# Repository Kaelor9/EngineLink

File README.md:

<h1 align="center">EngineLink</h1>

<p align="center">
  Dual-engine marine fuel monitoring on a custom ESP32-S3 board. It reads two engines over J1708, either Volvo Penta KAD / EDC I or SAE J1587. It shows live fuel flow on your phone and records every engine run, without an app, internet or cloud.
</p>

<p align="center">

</p>

<p align="center">
  
  <br>
  <sub>The phone app served by the board. <a href="https://kaelor9.github.io/EngineLink/demo/">Open the live demo</a> to use it in your browser against a simulated boat.</sub>
</p>

---

## About

**EngineLink** is a dedicated onboard device for boats with two engines. It reads fuel and engine data from two separate J1708 engine interfaces, processes it locally and serves a clean web app straight from the device.

The goal is **useful and trustworthy fuel consumption** rather than raw frames on a screen. If the engines do not send a value, or it is stale or invalid, EngineLink shows **—** and explains why. It never shows a made-up 0.

It is developed for a Fairline Targa 34 with 2 × **Volvo Penta KAD300 (EDC I)**. These engines use Volvo's request/response protocol. Scalings come from the owner's VODIA analysis. See [docs/KAD300_EDC1.md](docs/KAD300_EDC1.md).

---

## Why EngineLink?

Marine engine displays rarely show combined consumption, economy per nautical mile or a history you can export. Generic ESP32 boards need extra isolation and protection before they can be connected to an engine bus.

EngineLink combines both on one board:

- **galvanically isolated** J1708 transceivers, one per engine
- An isolated NMEA 2000 interface for GPS speed and time
- microSD storage for raw data, engine runs and calibration captures
- Its own Wi-Fi network, so it works with no router and no internet
- A phone-friendly web app stored on the device

---

## Key Features

- **Phone app "Engine Link":** Trip, Economy, Tank, History and Engines, add it to the home screen. Light, dark and night themes, metric or imperial, any currency
- **Live fuel flow:** per engine and combined L/h (KAD index 289 or J1587 PID 183)
- **Automatic trips** with notes (people, sea, wind), combine/split and CSV export
- **Fuel log and tank:** fuel aboard with an honest ±, range at the current speed
- **Self-calibrating fuel figures:** weighted fit over all fill-ups (topped up / clicked off), separate correction for idle, part load and cruise, odd fill-ups caught, every trip recalculated
- **Economy:** best cruising speed, trip planner, season statistics per RPM band, engine health trend
- **Volvo Penta KAD / EDC I:** VODIA scaling, passive decoding of an EDC display, or opt-in read-only polling
- **Calibration tools:** voltage check against a multimeter, fuel scale check, gear learned at the dock
- **Checked engine data:** physical limits and jump confirmation on every answer, short gaps bridged, faster reading while the throttle moves
- **Fuel economy:** L/nm when NMEA 2000 GPS speed is available
- **Lifetime totals** with engine hours that survive restarts and recalculate after calibration
- **Bus discovery:** every parameter your ECUs actually answer or send, with raw bytes
- **Guided engine test:** record steady RPM stages with your own reference readings, export CSV
- **Two Wi-Fi modes:** EngineLink's own network at `192.168.4.1` (factory default), or on the boat router at the address the router gives it. If the router is lost, EngineLink brings its own network back within two minutes and returns to the router by itself. Transmit power is tuned automatically.
- **Firmware updates from GitHub** over the boat router, with automatic rollback, or from a file
- **Reports to GitHub (optional):** with a token saved, EngineLink files an engine report after each trip and a Wi-Fi report after connection problems, so issues can be found without copying anything. No position, router name or password is ever included
- **Gear and clutch (DP drives):** every shift at idle is timed, from the gear bits to the propeller taking or losing load; a propeller that keeps pulling in neutral is listed under Events, and hard shifts (forward to reverse without a pause, shifts above idle) are counted
- **Guided drive test** at the dock or on open water, with small animations and safety steps: learns the gear and compressor bits and measures each drive
- **Four readings a second** of rpm, fuel, lever, boost and gear for each trip and around every event, with a report for the mechanic
- **Side by side:** idle fuel, compressor, boost, warm-up time and charging per engine
- **Diagnostics** with a setup check, connection tests and calibration

---

## Hardware

| Feature | Specification |
|---------|---------------|
| MCU | ESP32-S3-WROOM-1-N8R8 |
| Flash / PSRAM | 8 MB / 8 MB (OPI) |
| Engine inputs | 2 × isolated J1708 (MAX3444E + ADuM1201), J7 and J6 |
| Marine network | Isolated NMEA 2000 (ISO1042), listen-only |
| Storage | microSD (SPI) with card detect |
| Status | SK6805 addressable LED, level-shifted |
| Digital input | Optoisolated input on GPIO38 |
| Wireless | Wi-Fi 2.4 GHz access point + optional router |
| USB | USB-C, native USB CDC |
| Power | Polyfuse + TVS (SMCJ33CA) + reverse protection → LM5164 buck → 5 V → 3.3 V LDO |

### Pinout

| Connection | ESP32-S3 | Notes |
|------------|----------|-------|
| J7 · J1708 channel 1 | RX GPIO21 · TX GPIO47 | TX only while KAD polling runs; solder jumper SJ1 |
| J6 · J1708 channel 2 | RX GPIO17 · TX GPIO18 | TX only while KAD polling runs; solder jumper SJ2 |
| NMEA 2000 CAN | TX GPIO15 · RX GPIO16 | Listen-only when enabled |
| microSD | CS 10 · MOSI 11 · SCK 12 · MISO 13 · Detect 14 | Detect LOW = inserted |
| Status LED | GPIO48 | SK6805 |
| Isolated input | GPIO38 | |
| I²C | SDA 8 · SCL 9 | Unused, no RTC fitted |

On the schematic, channel 1 (J7) sits on the isolated domain named ISO2 and channel 2 (J6) on ISO1. This is cosmetic only. More detail and safety checks: [docs/HARDWARE.md](docs/HARDWARE.md).

---

## Software

The firmware is written for the ESP32-S3 with the Arduino framework. The complete web app (HTML, CSS and JavaScript) is embedded in flash, so it works without any internet connection.

| Page | What it shows |
|------|---------------|
| **Trip** | Fuel this trip, burn now against your average, cost, L/nm and range |
| **Economy** | Best cruising speed, trip planner, season statistics, insights |
| **Tank** | Fuel aboard, fuel log, how the estimate is made |
| **History** | All trips with notes, combine/split, CSV export |
| **Engines** | Every value per engine, engine sync, health trend, service |
| **Settings** | Units, currency, EngineLink Wi-Fi and boat router, firmware, diagnostics, SD card, backup and reset |

The app source is [`firmware/ui/app.html`](firmware/ui/app.html); `tools/build_ui.py` packs it gzip-compressed into `firmware/EngineLink/ui.h`. The firmware has one file per area (engines, fuel, trips, diagnosis, Wi-Fi, web API and so on); [HANDOVER.md](HANDOVER.md) describes the layout.

---

## Getting Started

1. **New boards only:** Open the **[web installer](https://kaelor9.github.io/EngineLink/)** in Chrome or Edge on a computer.
2. Connect the board with a USB-C data cable, tick the safety confirmation and click **Install**.
3. On your phone, join the Wi-Fi **EngineLink** (password `12345678`) and open **http://192.168.4.1**.
4. Complete the setup, then add **Engine Link** to the home screen (Settings shows how on iPhone and Android).
5. For Volvo Penta KAD300, follow the **[test procedure](docs/KAD300_EDC1.md#test-procedure-on-the-boat)**: listen, voltage check, RPM check, then tank to tank.

### Updating over Wi-Fi

You only need the cable once. For later versions:

- **With a boat router:** connect EngineLink to it under Settings → Boat router, then open **Settings → Firmware** and install the version you want. EngineLink downloads it from GitHub Releases. If the new version does not run properly for its first minute, EngineLink goes back to the previous one by itself.
- **Without a router:** download **`enginelink-update.bin`** from the [download page](https://kaelor9.github.io/EngineLink/#downloads), join the EngineLink Wi-Fi and choose the file under **Settings → Firmware**.

Settings, trips, the fuel log and fuel totals are kept with Wi-Fi application updates. **The full 8 MB USB installer overwrites NVS and LittleFS**, including stored data, even without a separate Erase Flash selection. If an existing board is locked out of Wi-Fi, use [USB recovery with backups](docs/USB_RECOVERY.md), not the full installer.

---

## Important Information

> [!IMPORTANT]
>
> EngineLink is **alpha firmware**. It has read both engines on the owner's boat, but it is not a validated product.
>
> - Disconnect the engine networks and NMEA 2000 during first flashing and bring-up
> - Measure **both** isolated 5 V supplies against **their own** isolated grounds (4.75–5.25 V) before connecting an engine
> - EngineLink only listens by default. **Reading the engines** (KAD polling) is a deliberate step: close the connector's jumper (SJ1/SJ2) and switch it on in Settings → Diagnostics with a confirmation. "Read engines automatically" is off until you turn it on. Only the read request `01 43 21` can be sent.
> - The KAD request format is reconstructed from Volvo's PC tool. The main values are confirmed on the boat; do the voltage check first on a new installation.
> - Do not poll while a Volvo diagnostic tool (VODIA) is connected
> - Change the factory Wi-Fi password `12345678` in Settings

See [KAD300 / EDC I](docs/KAD300_EDC1.md), [status and safety](docs/STATUS.md) and the [engine test procedure](docs/ENGINE_TEST.md).

---

## Project Status

| Hardware | Firmware | Engine validation |
|----------|----------|-------------------|
| ✅ Revision 1 assembled | 🚧 0.17.5 | 🚧 Both KAD300 engines read on the boat; tank-to-tank pending |

| Area | Status |
|------|--------|
| J1708 UART bench loop | Tested: 36,000 frames / 30 min / no recorded errors |
| microSD read/write | Bench tested |
| Status LED | Bench tested |
| Firmware build | CI compiled on every change |
| Router Wi-Fi | Tested on a Zyxel EX3600 (WPA2/WPA3 mixed): 500–630 kB/s, about 20 ms round trip on a free 2.4 GHz channel |
| KAD300 scaling (VODIA, M_902) | Confirmed from the database, fuel ×1/128 confirmed three ways |
| KAD request/reply on the wire | Works on both engines for rpm, fuel rate, temperatures, boost and battery; other values still to confirm |
| Fuel factor on the boat | Pending tank-to-tank |
| NMEA 2000 bus | Not yet validated |

---

## Roadmap

### Firmware

- [x] Offline web app with first-time setup
- [x] Dual-channel J1708 capture and SD logging
- [x] Guided engine test and calibration capture
- [x] Trip / lifetime totals and engine hours
- [x] Automatic engine-run log
- [x] Bus discovery
- [x] Wi-Fi firmware updates, from GitHub with rollback
- [x] Phone app with trips, fuel log, economy and engine health
- [x] Own Wi-Fi or boat router, with automatic fallback and return
- [x] Router mode validated on real hardware (WPA2, WPA3-capable routers)
- [x] Volvo Penta KAD / EDC I decoding and opt-in polling
- [x] KAD reply layout confirmed on the boat for the main values
- [x] Gear and clutch timing from the propeller load (DP drives)
- [ ] Remaining KAD values and status bits (263/264) decoded (gear and compressor bits learned per boat)
- [x] Engine and Wi-Fi reports to GitHub
- [ ] Fuel factor and corrections confirmed tank to tank
- [ ] NMEA 2000 output of engine and fuel data
- [ ] Settings authorization and unique device credentials

### Hardware

- [x] Revision 1 PCB
- [x] Isolated J1708 and NMEA 2000 interfaces
- [ ] Isolated supply verification on assembled boards
- [ ] NMEA 2000 isolated ground review (`GND_N2K_ISO`)
- [x] First field test on the boat

---

## Repository Structure

```text
.
├── .github/workflows/     # CI compile, validation and Pages publishing
├── docs/                  # KAD300/EDC I, hardware, alpha status, engine test, releasing
│   └── images/
├── experiments/           # Earlier bench Lab sketches (not the application)
├── firmware/
│   └── EngineLink/        # Application firmware (one file per area) + embedded web UI (ui.h)
├── hardware/              # Hardware notes
├── site/                  # GitHub Pages installer
├── HANDOVER.md            # Design decisions and constraints for developers
└── README.md
```

### Building locally

Arduino IDE or `arduino-cli` with the ESP32 core and the **Adafruit NeoPixel** library:

```bash
arduino-cli compile \
  --fqbn "esp32:esp32:esp32s3:FlashSize=8M,PartitionScheme=default_8MB,PSRAM=opi,USBMode=hwcdc,CDCOnBoot=cdc" \
  --build-property "compiler.c.elf.extra_flags=-Wl,--wrap=esp_wifi_init" \
  firmware/EngineLink
```

The version is defined once as `EL_VERSION` in `firmware/EngineLink/EngineLink.ino`. The installer and manifests take it from there. See [docs/RELEASING.md](docs/RELEASING.md). Release notes for every version are in [docs/releases](docs/releases).

---

## License

Licensing has not been selected yet. **Do not assume this repository is open source just because the code is visible on GitHub.**

---

<p align="center">
  Designed and developed by <strong>Kaelor9</strong>
  <br>
  ESP32-S3 • Marine Electronics • Dual-Engine Fuel Monitoring
</p>

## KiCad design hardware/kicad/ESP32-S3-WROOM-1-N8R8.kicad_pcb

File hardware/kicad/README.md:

# EngineLink — editable hardware design

Source: owner-supplied `ESP32-S3-WROOM-1-N8R8(9).zip`, reviewed 2026-11-10. The editable design was saved by KiCad 8.

## Files

- `ESP32-S3-WROOM-1-N8R8.kicad_pro` — KiCad project settings.
- `ESP32-S3-WROOM-1-N8R8.kicad_sch` — editable electrical schematic.
- `ESP32-S3-WROOM-1-N8R8.kicad_pcb` — editable PCB design (4 copper layers, KiCad 8 format).
- `ESP32-S3-WROOM-1-N8R8.kicad_dru` — original KiCad design rules; check them against the intended insulation specification.
- `bom/ibom.html` — standalone interactive BOM/placement viewer (open locally in a browser).

The source archive also contained 28 historical backup ZIPs, a footprint cache, `.kicad_prl` per-user editor preferences, and `.lck` locks; these are omitted. The newest backup (`2026-11-07_123455`) matches the four editable files byte-for-byte.

This import does **not** include current manufacturing Gerber/drill exports, a validated purchase-ready BOM, or a complete ERC/DRC report. Earlier Gerber reviews in this repo are historical evidence, not manufacturing approval. These original KiCad files have been preserved unchanged and have not yet been independently validated.

## Opening

Open `ESP32-S3-WROOM-1-N8R8.kicad_pro` in KiCad 8 or newer. Some 3D model paths may require installed KiCad or vendor libraries; check visually. Export Gerber/drill/BOM from the verified board revision rather than using old production archives.

See `SHA256SUMS.txt` for checksums of the unmodified files extracted from the owner's ZIP.

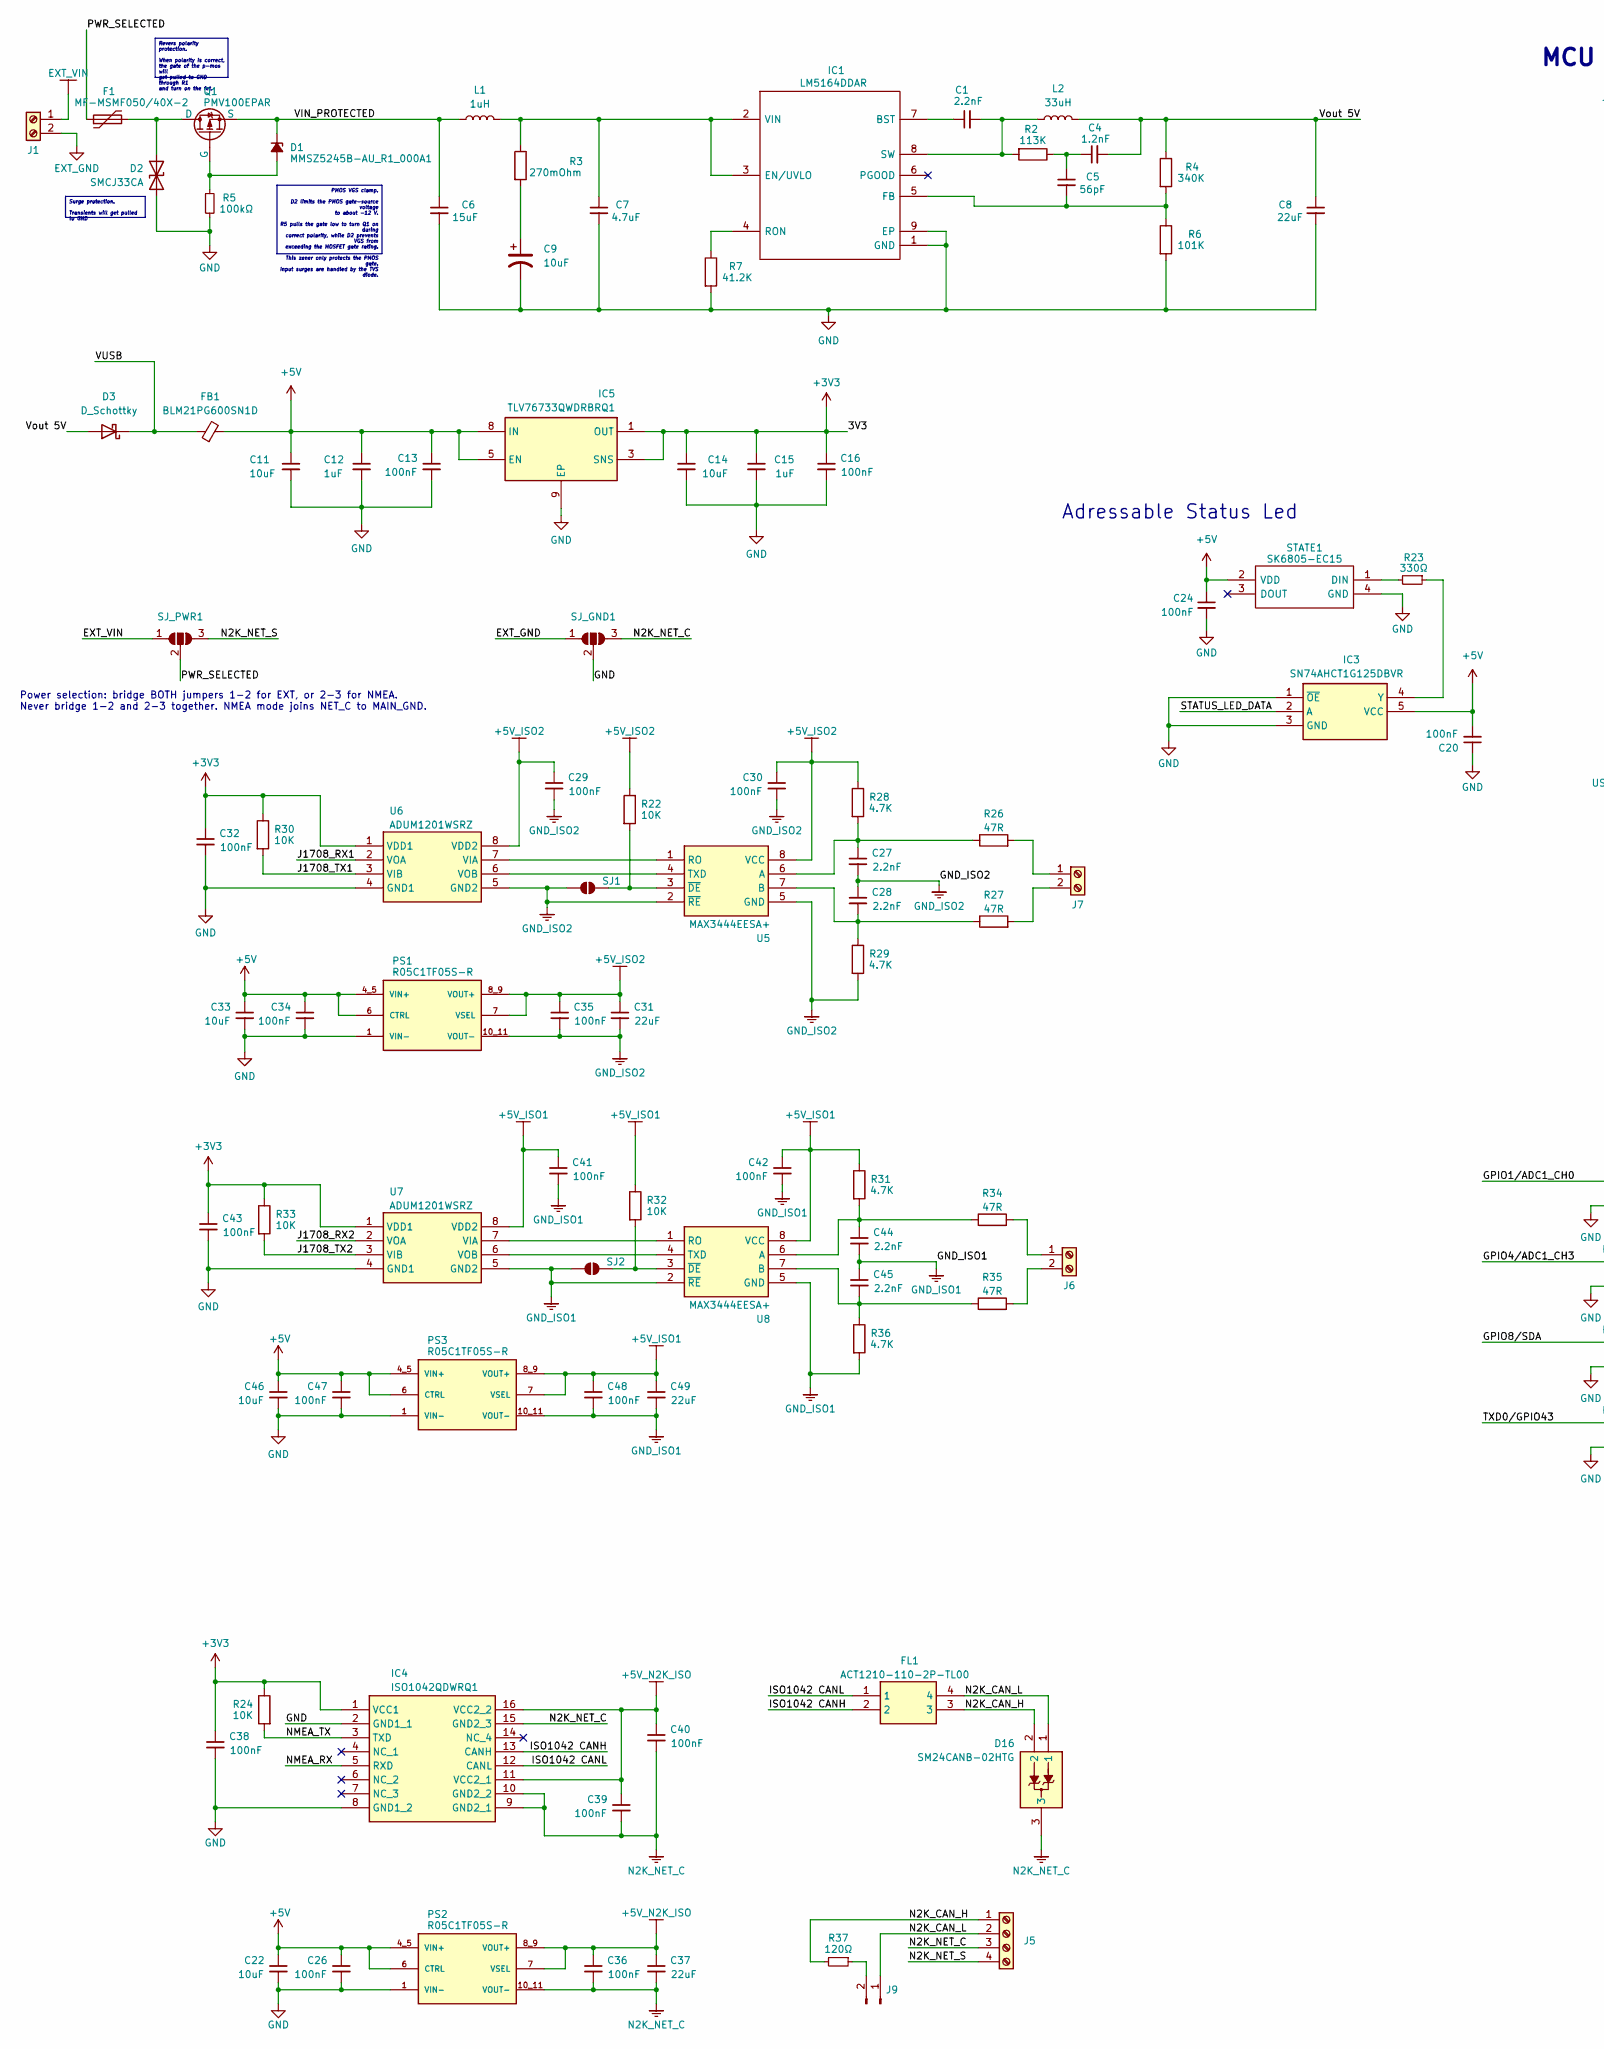
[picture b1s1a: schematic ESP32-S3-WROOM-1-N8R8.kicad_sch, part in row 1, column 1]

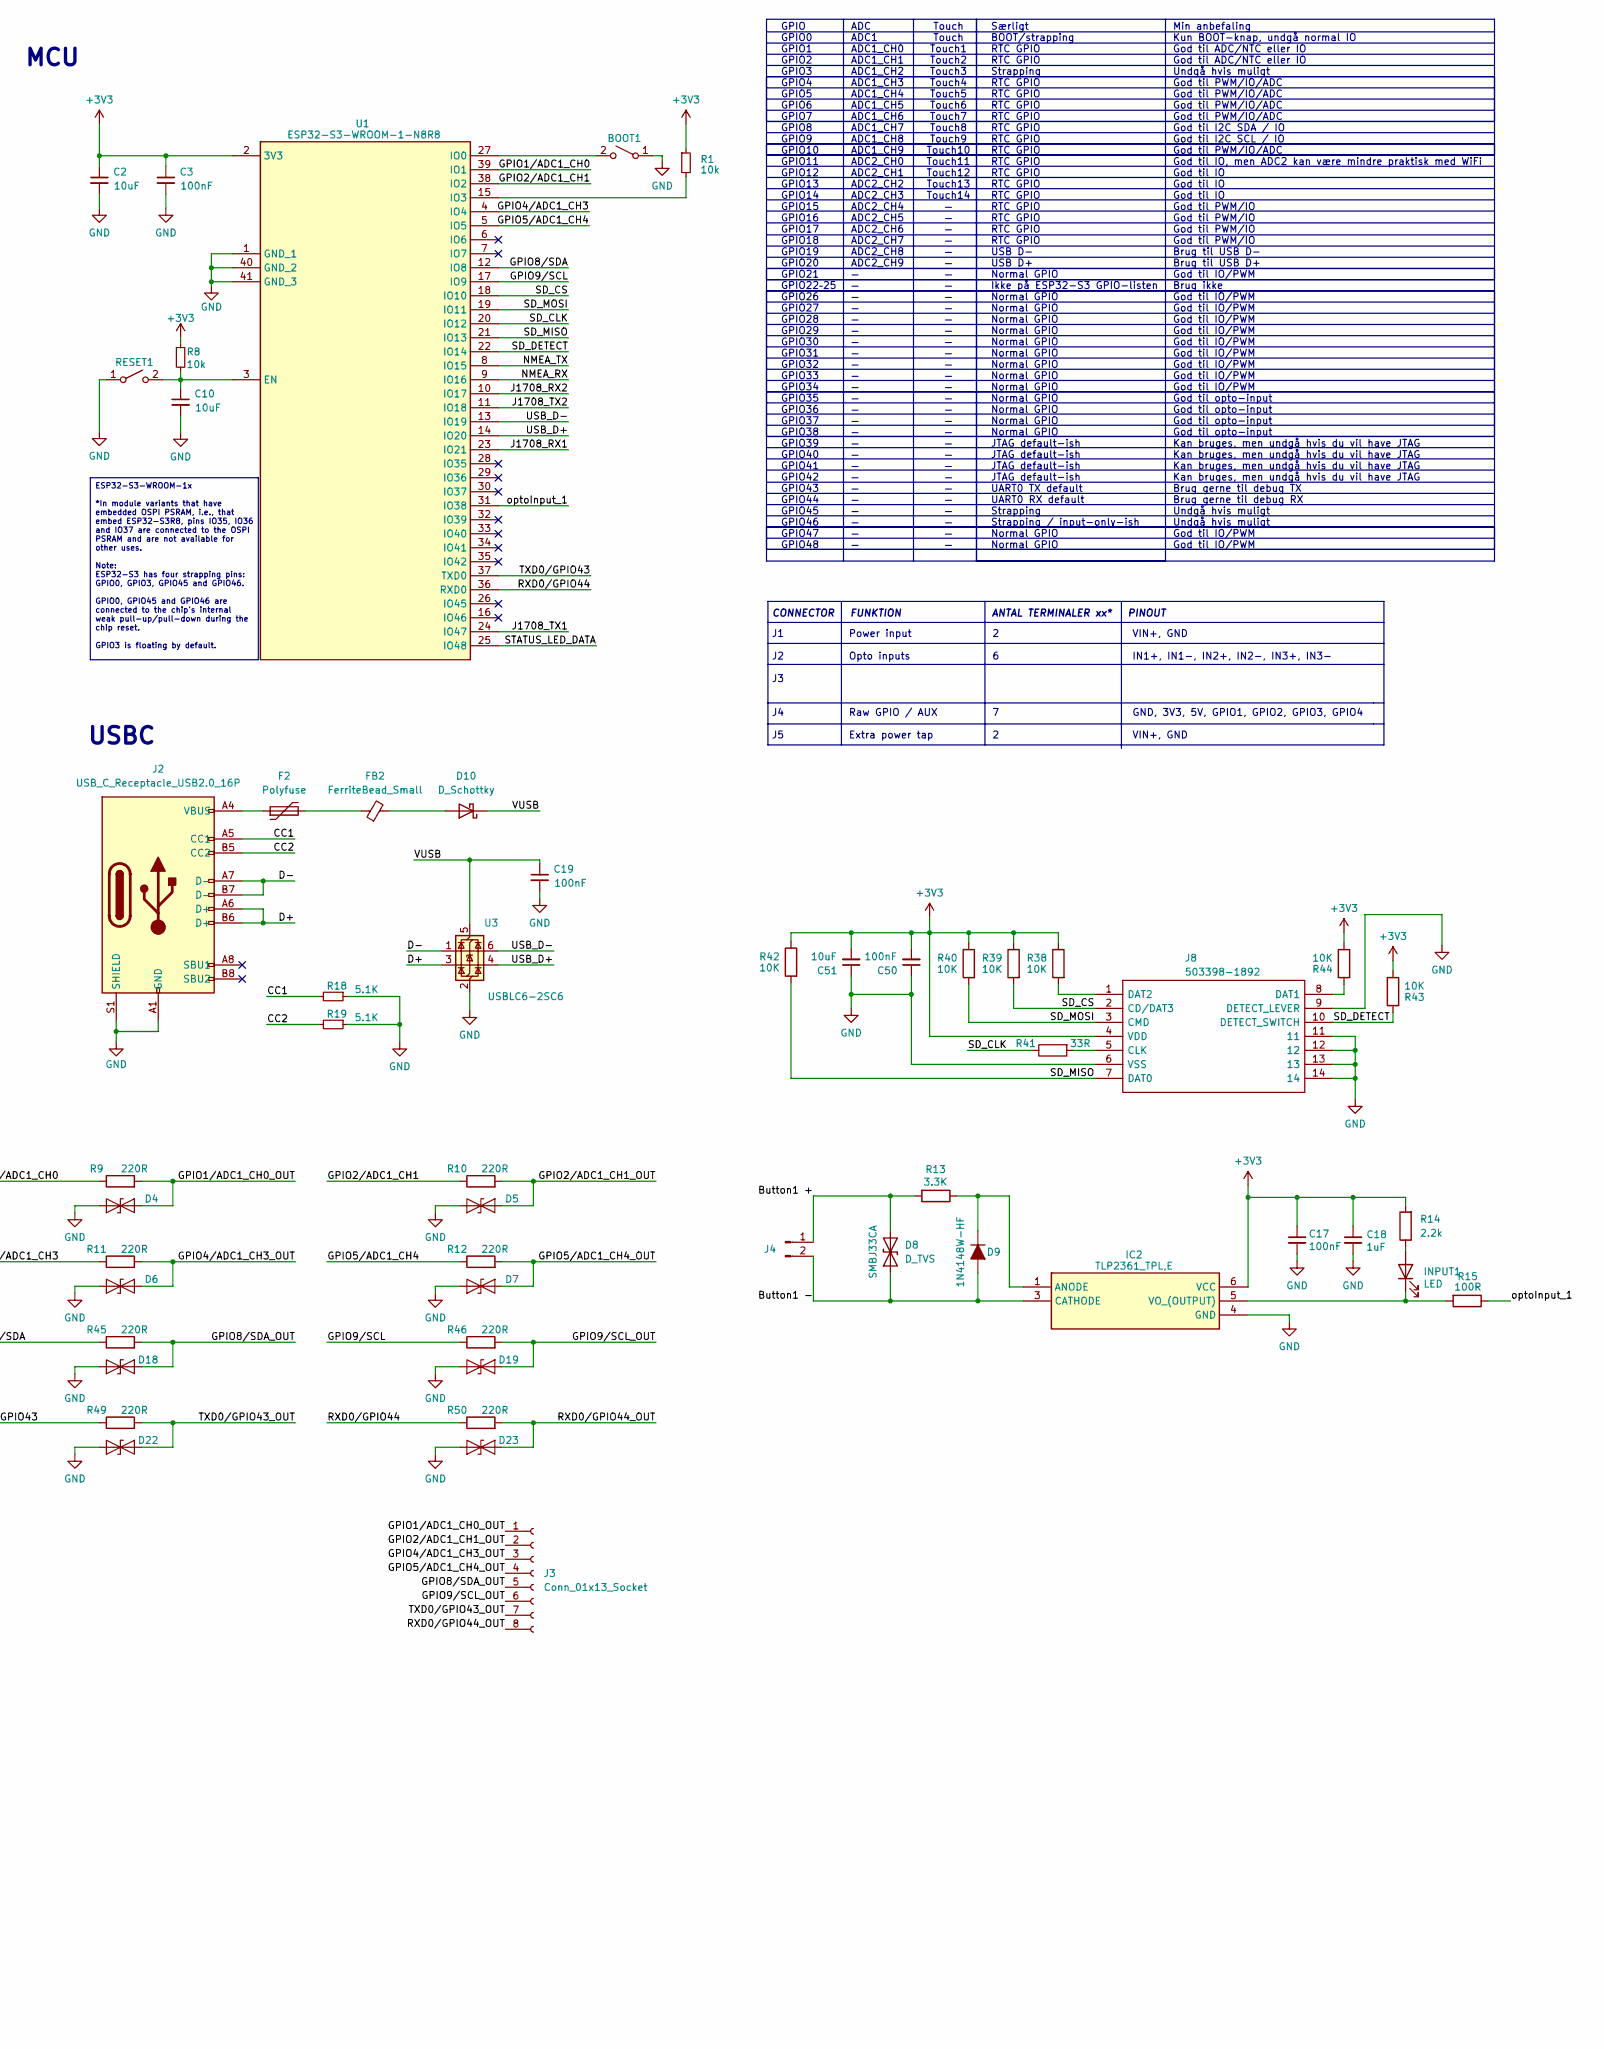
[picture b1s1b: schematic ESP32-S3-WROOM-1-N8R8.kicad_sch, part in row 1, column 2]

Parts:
BOOT1: PTS810SJM250SMTRLFS
C1: 2.2nF; C_0805_2012Metric; Voltage Rating VDC 50V
C2, C10, C51: 10uF; C_0603_1608Metric; Voltage Rating VDC 25V
C3, C13, C16, C17, C19, C20, C26, C29, C30, C32, C34, C35, C36, C38, C39, C40, C41, C42, C43, C47, C48, C50: 100nF; C_0603_1608Metric; Voltage Rating VDC 50V
C4: 1.2nF; C_0402_1005Metric; Voltage Rating VDC 50V
C5: 56pF; C_0805_2012Metric; Voltage Rating VDC 50V
C6: 15uF; C_2220_5750Metric; Voltage Rating VDC 100V
C7: 4.7uF; C_1206_3216Metric; Voltage Rating VDC 50V
C8: 22uF; C_1206_3216Metric; Voltage Rating VDC 10V
C9: 10uF; CAPAE660X610N; Voltage Rating VDC 50V
C11, C14: 10uF; C_1206_3216Metric; Voltage Rating VDC 16V
C12, C15: 1uF; C_0805_2012Metric; Voltage Rating VDC 25V
C18: 1uF; C_0805_2012Metric; Voltage Rating VDC 50V
C22, C33, C46: 10uF; C_0805_2012Metric; Voltage Rating VDC 10V
C24: 100nF; C_0402_1005Metric; Voltage Rating VDC 50V
C27, C28, C44, C45: 2.2nF; C_0603_1608Metric; Voltage Rating VDC 50V
C31, C37, C49: 22uF; C_1206_3216Metric; Voltage Rating VDC 50V
D1: MMSZ5245B-AU_R1_000A1; D_SOD-123
D2: SMCJ33CA; D_SMC
D3, D10: D_Schottky; D_SOD-123
D4, D5, D6, D7, D18, D19, D22, D23: SD05_SOD323; D_SOD-323
D8: D_TVS; D_SMB
D9: D_SOD-123
D16: SM24CANB-02HTG; SM24CANB02HTG
F1: MF-MSMF050/40X-2; MFMSMF05040X2
F2: Polyfuse; Fuse_1206_3216Metric
FB1: BLM21PG600SN1D; R_0805_2012Metric
FB2: FerriteBead_Small; R_0805_2012Metric
FL1: ACT1210-110-2P-TL00; ACT12101102PTL00
IC1: LM5164DDAR; SOIC127P600X170-9N
IC2: TLP2361_TPL,E; 11-4L1S_5-PIN-SOIC_
IC3: SN74AHCT1G125DBVR; SOT95P280X145-5N
IC4: ISO1042QDWRQ1; SOIC127P1030X265-16N
IC5: TLV76733QWDRBRQ1; SON65P300X300X100-9N-D
INPUT1: LED; LED_0603_1608Metric
J1, J6, J7: Screw_Terminal_01x02; 1757242
J2: USB_C_Receptacle_USB2.0_16P; USB494000A
J3: Conn_01x13_Socket; PinHeader_1x08_P2.54mm_Vertical
J4, J9: Conn_01x02_Pin; PinHeader_1x02_P2.54mm_Vertical
J5: 1757268
J8: 503398-1892; 5033981892
L1: 1uH; L_1008_2520Metric
L2: 33uH; 3232 (8282 metric)
PS1, PS2, PS3: R05C1TF05S-R; CONV_R05C1TF05S-R
Q1: PMV100EPAR; TSOT-23
R1, R8: 10k; R_0603_1608Metric
R2: 113K; R_0603_1608Metric
R3: 270mOhm; R_0603_1608Metric
R4: 340K; R_0603_1608Metric
R5: 100kΩ; R_0402_1005Metric
R6: 101K; R_0805_2012Metric
R7: 41.2K; R_0805_2012Metric
R9, R10, R11, R12, R45, R46, R49, R50: 220R; R_0805_2012Metric; Voltage Rating VDC 150V
R13: 3.3K; R_1206_3216Metric
R14: 2.2k; R_0603_1608Metric
R15: 100R; R_0603_1608Metric
R18, R19: 5.1K; R_0603_1608Metric; Voltage Rating VDC 150V
R22, R24, R30, R32, R33, R38, R39, R40, R42, R43, R44: 10K; R_0603_1608Metric
R23: 330Ω; R_0402_1005Metric
R26, R27, R34, R35: 47R; R_0603_1608Metric
R28, R29, R31, R36: 4.7K; R_0603_1608Metric
R37: 120Ω; R_0603_1608Metric
R41: 33R; R_0603_1608Metric
RESET1: PTS810SJM250SMTRLFS
SJ1, SJ2: SJ1J1708_TX_ENABLE; SolderJumper-2_P1.3mm_Open_TrianglePad1.0x1.5mm
SJ_GND1: SolderJumper_3_Open; SolderJumper-3_P1.3mm_Open_Pad1.0x1.5mm_NumberLabels
SJ_PWR1: SolderJumper_3_Open; SolderJumper-3_P1.3mm_Open_Pad1.0x1.5mm_NumberLabels
STATE1: SK6805-EC15; SK6805EC15
U1: ESP32-S3-WROOM-1-N8R8; ESP32S3WROOM1N8R8
U3: USBLC6-2SC6; SOT-23-6
U5, U8: MAX3444EESA+; SOIC127P600X175-8N
U6, U7: ADUM1201WSRZ; SOIC127P600X175-8N

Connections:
+3V3: C2.1, C3.1, C14.1, C15.1, C16.1, C17.1, C18.1, C32.1, C38.1, C43.1, C50.2, C51.2, IC2.6 (VCC), IC4.1 (VCC1), IC5.1 (OUT), IC5.3 (SNS), J8.4 (VDD), R1.1, R8.1, R14.2, R24.1, R30.1, R33.1, R38.1, R39.1, R40.1, R42.1, R43.2, R44.2, U1.2 (3V3), U6.1 (VDD1), U7.1 (VDD1)
+5V: C11.1, C12.1, C13.1, C20.2, C22.1, C24.1, C26.1, C33.1, C34.1, C46.1, C47.1, FB1.2, IC3.5 (VCC), IC5.5 (EN), IC5.8 (IN), PS1.4_5 (VIN+), PS1.6 (CTRL), PS2.4_5 (VIN+), PS2.6 (CTRL), PS3.4_5 (VIN+), PS3.6 (CTRL), STATE1.2 (VDD)
+5V_ISO1: C41.1, C42.1, C48.1, C49.1, PS3.7 (VSEL), PS3.8_9 (VOUT+), R31.1, R32.1, U7.8 (VDD2), U8.8 (VCC)
+5V_ISO2: C29.1, C30.1, C31.1, C35.1, PS1.7 (VSEL), PS1.8_9 (VOUT+), R22.1, R28.1, U5.8 (VCC), U6.8 (VDD2)
+5V_N2K_ISO: C36.1, C37.1, C39.1, C40.1, IC4.11 (VCC2_1), IC4.16 (VCC2_2), PS2.7 (VSEL), PS2.8_9 (VOUT+)
/Button1 +: D8.2 (A2), J4.1, R13.2
/Button1 -: D8.1 (A1), D9.2 (A), IC2.3 (CATHODE), J4.2
/CC1: J2.A5 (CC1), R18.2
/CC2: J2.B5 (CC2), R19.2
/D+: J2.A6 (D+), J2.B6 (D+), U3.3 (I/O2)
/D-: J2.A7 (D-), J2.B7 (D-), U3.1 (I/O1)
/GPIO1/ADC1_CH0: R9.1, U1.39 (IO1)
/GPIO1/ADC1_CH0_OUT: D4.2 (A2), J3.1, R9.2
/GPIO2/ADC1_CH1: R10.1, U1.38 (IO2)
/GPIO2/ADC1_CH1_OUT: D5.2 (A2), J3.2, R10.2
/GPIO4/ADC1_CH3: R11.1, U1.4 (IO4)
/GPIO4/ADC1_CH3_OUT: D6.2 (A2), J3.3, R11.2
/GPIO5/ADC1_CH4: R12.1, U1.5 (IO5)
/GPIO5/ADC1_CH4_OUT: D7.2 (A2), J3.4, R12.2
/GPIO6/ADC1_CH5: U1.6 (IO6)
/GPIO7/ADC1_CH6: U1.7 (IO7)
/GPIO8/SDA: R45.1, U1.12 (IO8)
/GPIO8/SDA_OUT: D18.2 (A2), J3.5, R45.2
/GPIO9/SCL: R46.1, U1.17 (IO9)
/GPIO9/SCL_OUT: D19.2 (A2), J3.6, R46.2
/GPIO40: U1.33 (IO40)
/GPIO41: U1.34 (IO41)
/GPIO42: U1.35 (IO42)
/ISO1042 CANH: FL1.2, IC4.13 (CANH)
/ISO1042 CANL: FL1.1, IC4.12 (CANL)
/J1708_RX1: U1.23 (IO21), U6.2 (VOA)
/J1708_RX2: U1.10 (IO17), U7.2 (VOA)
/J1708_TX1: R30.2, U1.24 (IO47), U6.3 (VIB)
/J1708_TX2: R33.2, U1.11 (IO18), U7.3 (VIB)
/N2K_CAN_H: D16.2, FL1.3, J5.1, R37.2
/N2K_CAN_L: D16.1, FL1.4, J5.2, J9.1
/N2K_NET_S: J5.4, SJ_PWR1.3 (B)
/NMEA_RX: IC4.5 (RXD), U1.9 (IO16)
/NMEA_TX: IC4.3 (TXD), R24.2, U1.8 (IO15)
/PWR_SELECTED: F1.1, SJ_PWR1.2 (C)
/RXD0/GPIO44: R50.1, U1.36 (RXD0)
/RXD0/GPIO44_OUT: D23.2 (A2), J3.8, R50.2
/SD_CLK: R41.1, U1.20 (IO12)
/SD_CS: J8.2 (CD/DAT3), R39.2, U1.18 (IO10)
/SD_DETECT: J8.10 (DETECT_SWITCH), R43.1, U1.22 (IO14)
/SD_MISO: J8.7 (DAT0), R42.2, U1.21 (IO13)
/SD_MOSI: J8.3 (CMD), R40.2, U1.19 (IO11)
/STATUS_LED_DATA: IC3.2 (A), U1.25 (IO48)
/TXD0/GPIO43: R49.1, U1.37 (TXD0)
/TXD0/GPIO43_OUT: D22.2 (A2), J3.7, R49.2
/USB_D+: U1.14 (IO20), U3.4 (I/O2)
/USB_D-: U1.13 (IO19), U3.6 (I/O1)
/VIN_PROTECTED: C6.1, D1.1 (K), L1.1, Q1.2 (S)
/VUSB: C19.1, D3.1 (K), D10.1 (K), FB1.1, U3.5 (VBUS)
/Vout 5V: C4.2, C8.1, D3.2 (A), L2.2, R4.1
/optoInput_1: R15.1, U1.31 (IO38)
EXT_GND: J1.2, SJ_GND1.1 (A)
EXT_VIN: J1.1, SJ_PWR1.1 (A)
GND: BOOT1.1 (A), C2.2, C3.2, C6.2, C7.2, C8.2, C9.2, C10.2, C11.2, C12.2, C13.2, C14.2, C15.2, C16.2, C17.2, C18.2, C19.2, C20.1, C22.2, C24.2, C26.2, C32.2, C33.2, C34.2, C38.2, C43.2, C46.2, C47.2, C50.1, C51.1, D2.2 (A2), D4.1 (A1), D5.1 (A1), D6.1 (A1), D7.1 (A1), D18.1 (A1), D19.1 (A1), D22.1 (A1), D23.1 (A1), IC1.1 (GND), IC1.9 (EP), IC2.4 (GND), IC3.1 (~OE), IC3.3 (GND), IC4.2 (GND1_1), IC4.8 (GND1_2), IC5.4 (GND_1), IC5.6 (GND_2), IC5.9 (EP), J2.A1 (GND), J2.A12 (GND), J2.B1 (GND), J2.B12 (GND), J2.S1 (SHIELD), J8.6 (VSS), J8.9 (DETECT_LEVER), J8.11, J8.12, J8.13, J8.14, PS1.1 (VIN-), PS1.2_3 (VIN-), PS2.1 (VIN-), PS2.2_3 (VIN-), PS3.1 (VIN-), PS3.2_3 (VIN-), R5.2, R6.2, R7.2, R18.1, R19.1, RESET1.1 (A), SJ_GND1.2 (C), STATE1.4 (GND), U1.1 (GND_1), U1.40 (GND_2), U1.41 (GND_3), U1.42 (GND_4), U1.43 (GND_5), U1.44 (GND_6), U1.45 (GND_7), U1.46 (GND_8), U1.47 (GND_9), U1.48 (GND_10), U1.49 (GND_11), U3.2 (GND), U6.4 (GND1), U7.4 (GND1)
GND_ISO1: C41.2, C42.2, C44.2, C45.1, C48.2, C49.2, PS3.10_11 (VOUT-), PS3.12 (VOUT-), R36.2, SJ2.1 (A), U7.5 (GND2), U8.2 (~RE), U8.5 (GND)
GND_ISO2: C27.2, C28.1, C29.2, C30.2, C31.2, C35.2, PS1.10_11 (VOUT-), PS1.12 (VOUT-), R29.2, SJ1.1 (A), U5.2 (~RE), U5.5 (GND), U6.5 (GND2)
N2K_NET_C: C36.2, C37.2, C39.2, C40.2, D16.3, IC4.9 (GND2_1), IC4.10 (GND2_2), IC4.15 (GND2_3), J5.3, PS2.10_11 (VOUT-), PS2.12 (VOUT-), SJ_GND1.3 (B)
unnamed: BOOT1.2 (B), U1.27 (IO0)
unnamed: C4.1, C5.1, R2.1
unnamed: C9.1, R3.2
unnamed: D1.2 (A), Q1.1 (G), R5.1
unnamed: D2.1 (A1), F1.2, Q1.3 (D)
unnamed: D9.1 (K), IC2.1 (ANODE), R13.1
unnamed: D10.2 (A), FB2.2
unnamed: F2.1, J2.A4 (VBUS), J2.A9 (VBUS), J2.B4 (VBUS), J2.B9 (VBUS)
unnamed: F2.2, FB2.1
unnamed: C1.1, IC1.7 (BST)
unnamed: C7.1, IC1.2 (VIN), IC1.3 (EN/UVLO), L1.2, R3.1
unnamed: C5.2, IC1.5 (FB), R4.2, R6.1
unnamed: IC1.4 (RON), R7.1
unnamed: C1.2, IC1.8 (SW), L2.1, R2.2
unnamed: IC2.5 (VO_(OUTPUT)), INPUT1.1 (K), R15.2
unnamed: IC3.4 (Y), R23.1
unnamed: INPUT1.2 (A), R14.1
unnamed: J6.1, R34.2
unnamed: J6.2, R35.2
unnamed: J7.1, R26.2
unnamed: J7.2, R27.2
unnamed: J8.5 (CLK), R41.2
unnamed: J8.8 (DAT1), R44.1
unnamed: J8.1 (DAT2), R38.2
unnamed: J9.2, R37.1
unnamed: C10.1, R8.2, RESET1.2 (B), U1.3 (EN)
unnamed: R22.2, SJ1.2 (B), U5.3 (~DE)
unnamed: R32.2, SJ2.2 (B), U8.3 (~DE)
unnamed: R23.2, STATE1.1 (DIN)
unnamed: R1.2, U1.15 (IO3)
unnamed: C27.1, R26.1, R28.2, U5.6 (A)
unnamed: C28.2, R27.1, R29.1, U5.7 (B)
unnamed: U5.1 (RO), U6.7 (VIA)
unnamed: U5.4 (TXD), U6.6 (VOB)
unnamed: U7.7 (VIA), U8.1 (RO)
unnamed: U7.6 (VOB), U8.4 (TXD)
unnamed: C44.1, R31.2, R34.1, U8.6 (A)
unnamed: C45.2, R35.1, R36.1, U8.7 (B)

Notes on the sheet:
Revers polarity protection. When polarity is correct, the gate of the p-mos will get pulled to GND through R1 and turn on the fet.
ESP32-S3-WROOM-1x *In module variants that have embedded OSPI PSRAM, i.e., that embed ESP32-S3R8, pins IO35, IO36 and IO37 are connected to the OSPI PSRAM and are not available for other uses. Note: ESP32-S3 has four strapping pins: GPIO0, GPIO3, GPIO45 and GPIO46. GPIO0, GPIO45 and GPIO46 are conn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
PMOS VGS clamp. D2 limits the PMOS gate-source voltage to about -12 V. R5 pulls the gate low to turn Q1 on during correct polarity, while D2 prevents VGS from exceeding the MOSFET gate rating. This zener only protects the PMOS gate. Input surges are handled by the TVS diode.
Surge protection. Transients will get pulled to GND
GPIO GPIO0 GPIO1 GPIO2 GPIO3 GPIO4 GPIO5 GPIO6 GPIO7 GPIO8 GPIO9 GPIO10 GPIO11 GPIO12 GPIO13 GPIO14 GPIO15 GPIO16 GPIO17 GPIO18 GPIO19 GPIO20 GPIO21 GPIO22–25 GPIO26 GPIO27 GPIO28 GPIO29 GPIO30 GPIO31 GPIO32 GPIO33 GPIO34 GPIO35 GPIO36 GPIO37 GPIO38 GPIO39 GPIO40 GPIO41 GPIO42 GPIO43 GPIO44 GPIO45 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
MCU
Power selection: bridge BOTH jumpers 1-2 for EXT, or 2-3 for NMEA. Never bridge 1-2 and 2-3 together. NMEA mode joins NET_C to MAIN_GND.
CONNECTOR FUNKTION ANTAL TERMINALER xx* PINOUT
Min anbefaling Kun BOOT-knap, undgå normal IO God til ADC/NTC eller IO God til ADC/NTC eller IO Undgå hvis muligt God til PWM/IO/ADC God til PWM/IO/ADC God til PWM/IO/ADC God til PWM/IO/ADC God til I2C SDA / IO God til I2C SCL / IO God til PWM/IO/ADC God til IO, men ADC2 kan være mindre praktisk me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
USBC
J1 J2 J3 J4 J5
ADC ADC1 ADC1_CH0 ADC1_CH1 ADC1_CH2 ADC1_CH3 ADC1_CH4 ADC1_CH5 ADC1_CH6 ADC1_CH7 ADC1_CH8 ADC1_CH9 ADC2_CH0 ADC2_CH1 ADC2_CH2 ADC2_CH3 ADC2_CH4 ADC2_CH5 ADC2_CH6 ADC2_CH7 ADC2_CH8 ADC2_CH9 — — — — — — — — — — — — — — — — — — — — — — — — —
VIN+, GND IN1+, IN1-, IN2+, IN2-, IN3+, IN3- GND, 3V3, 5V, GPIO1, GPIO2, GPIO3, GPIO4 VIN+, GND
Touch Touch Touch1 Touch2 Touch3 Touch4 Touch5 Touch6 Touch7 Touch8 Touch9 Touch10 Touch11 Touch12 Touch13 Touch14 — — — — — — — — — — — — — — — — — — — — — — — — — — — — — — —
Adressable Status Led
2 6 7 2
Særligt BOOT/strapping RTC GPIO RTC GPIO Strapping RTC GPIO RTC GPIO RTC GPIO RTC GPIO RTC GPIO RTC GPIO RTC GPIO RTC GPIO RTC GPIO RTC GPIO RTC GPIO RTC GPIO RTC GPIO RTC GPIO RTC GPIO USB D- USB D+ Normal GPIO Ikke på ESP32-S3 GPIO-listen Normal GPIO Normal GPIO Normal GPIO Normal GPIO Normal GPI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
Power input Opto inputs Raw GPIO / AUX Extra power tap

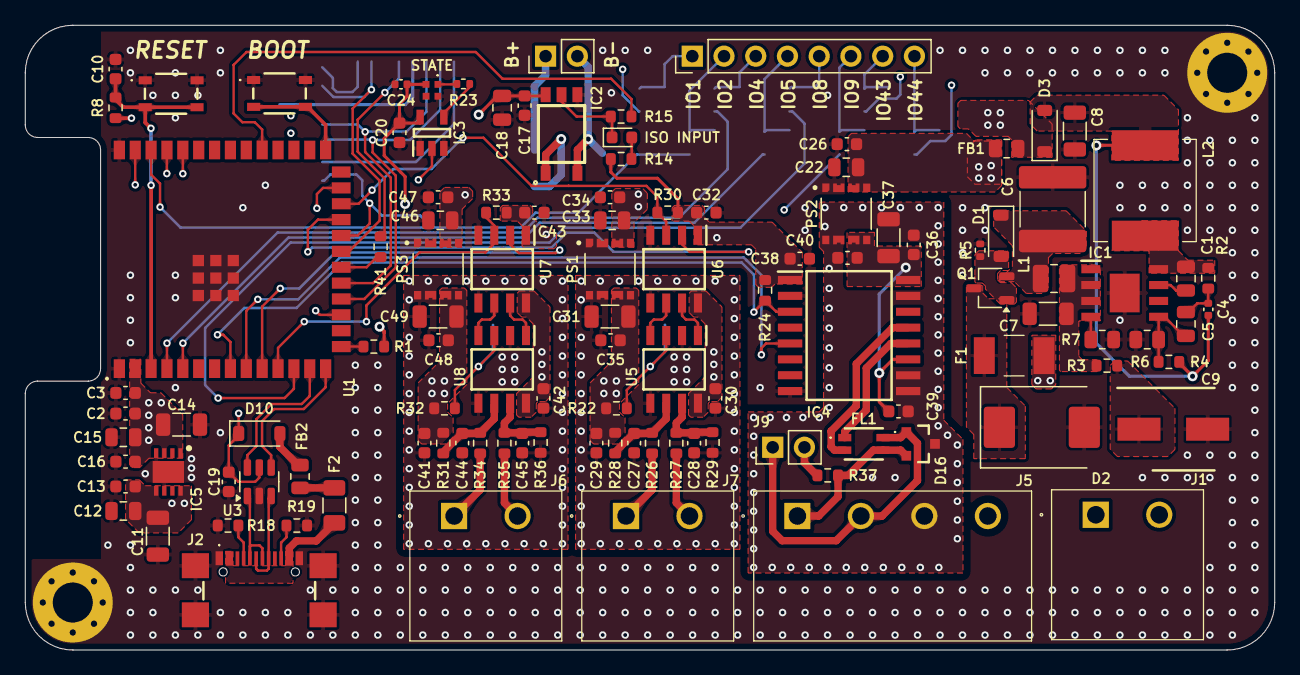
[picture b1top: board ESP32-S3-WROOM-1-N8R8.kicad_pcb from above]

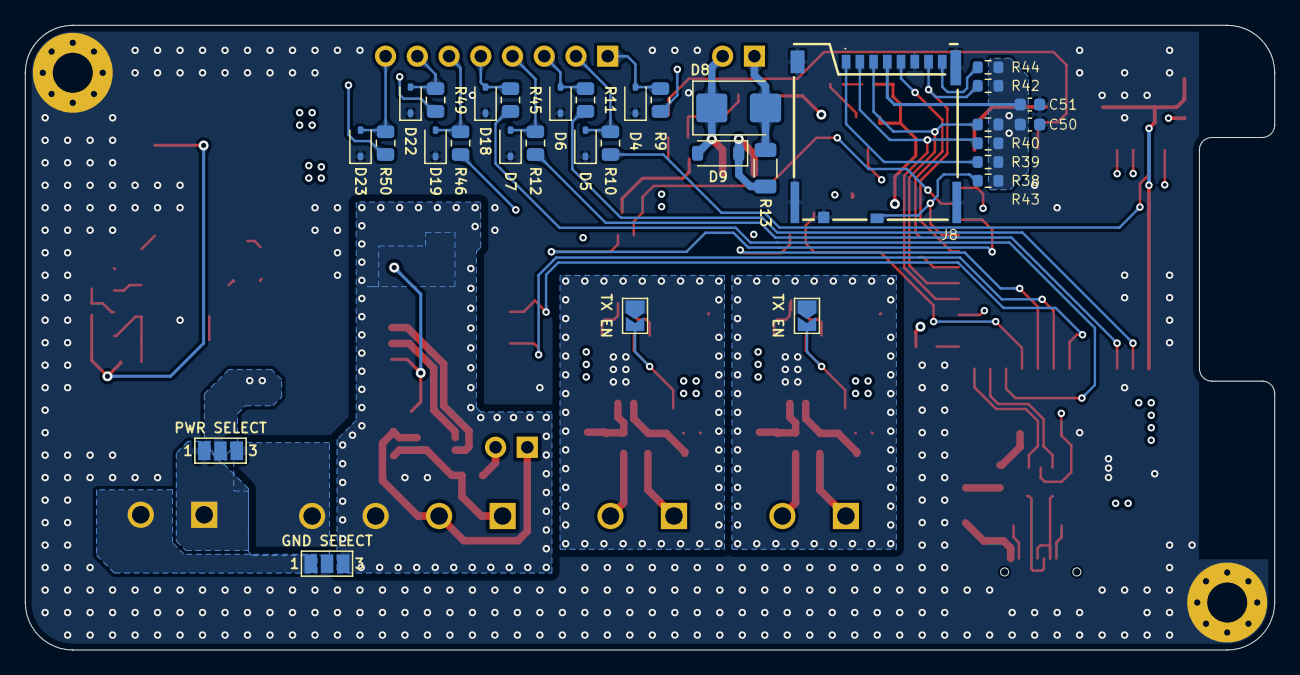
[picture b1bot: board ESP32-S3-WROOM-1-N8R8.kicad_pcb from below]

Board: 4 copper layers, 100.0 x 50.0 mm, 145 parts (32 on the bottom side), 95 nets.

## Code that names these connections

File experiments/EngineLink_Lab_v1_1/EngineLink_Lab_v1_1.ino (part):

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constexpr uint8_t PIN_J7_RX = 21, PIN_J7_TX = 47; // J1708 #1
constexpr uint8_t PIN_J6_RX = 17, PIN_J6_TX = 18; // J1708 #2
constexpr uint8_t PIN_LED = 48;
constexpr uint8_t PIN_SD_CS = 10, PIN_SD_MOSI = 11;
constexpr uint8_t PIN_SD_SCK = 12, PIN_SD_MISO = 13, PIN_SD_DETECT = 14;
constexpr uint8_t PIN_OPTO = 38;
constexpr uint8_t PIN_CAN_TX = 15, PIN_CAN_RX = 16; // NOT USED in this version
constexpr uint32_t BUS_BAUD = 9600;
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  setPixel(led.Color((color >> 16) & 255, (color >> 8) & 255, color & 255));
}

bool cardPresent() { return digitalRead(PIN_SD_DETECT) == LOW; }
void stopLogging() { if (sdLogging) { csv.flush(); csv.close(); sdLogging = false; } }

bool mountSD() {
  if (!cardPresent()) { sdMessage = "Kort mangler"; return false; }
  if (sdMounted) return true;
  SPI.begin(PIN_SD_SCK, PIN_SD_MISO, PIN_SD_MOSI, PIN_SD_CS);
  sdMounted = SD.begin(PIN_SD_CS, SPI, 4000000);
  sdMessage = sdMounted ? "SD monteret ved 4 MHz" : "SD.begin fejlede";
  return sdMounted;
}
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  Serial.begin(115200);
  delay(5000); // Prior S3 tests needed time for USB CDC monitor to connect.
  Serial.println("\n=== EngineLink Lab v1.1 ===");
  pinMode(PIN_SD_DETECT, INPUT); // PCB has external 10k pull-up
  pinMode(PIN_OPTO, INPUT);
  j7.begin(BUS_BAUD, SERIAL_8N1, PIN_J7_RX, PIN_J7_TX);
  j6.begin(BUS_BAUD, SERIAL_8N1, PIN_J6_RX, PIN_J6_TX);
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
